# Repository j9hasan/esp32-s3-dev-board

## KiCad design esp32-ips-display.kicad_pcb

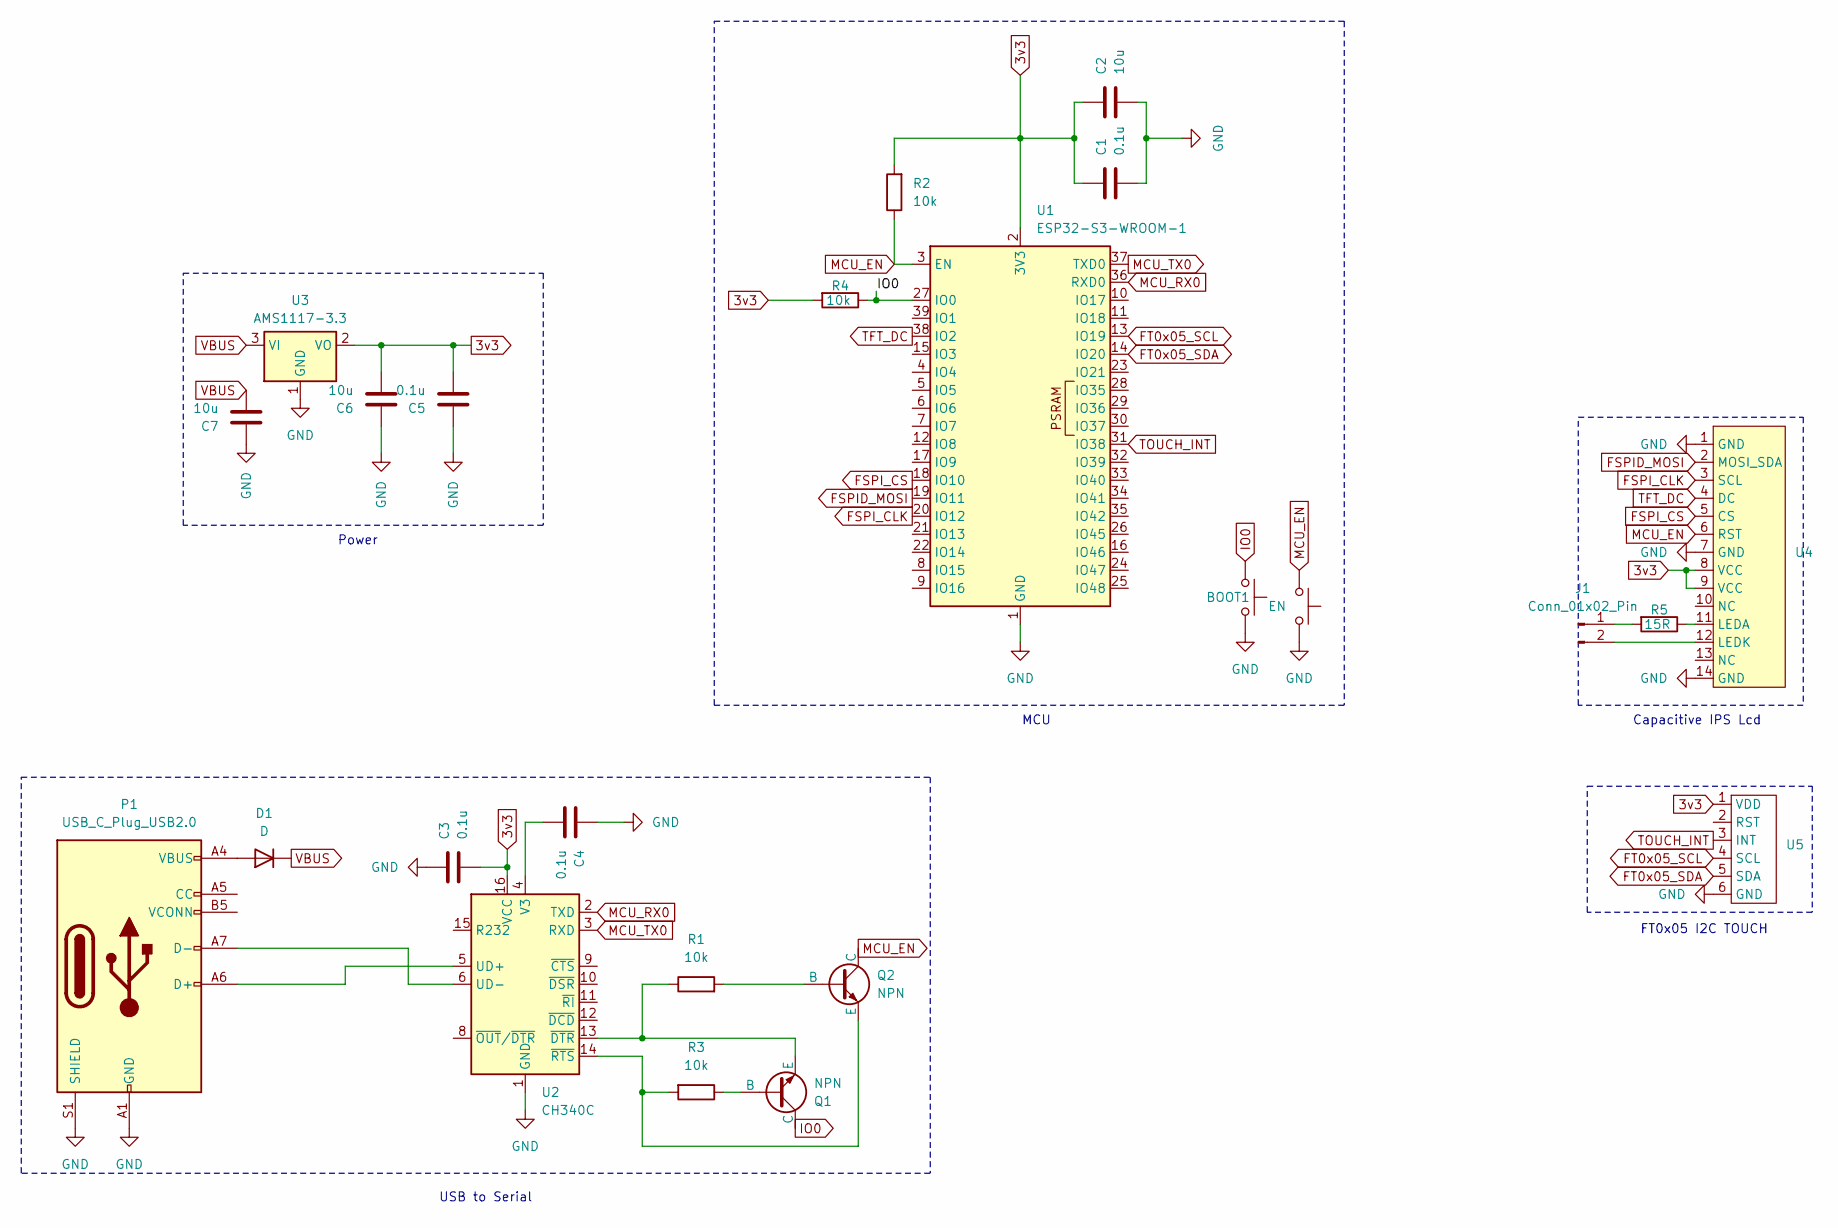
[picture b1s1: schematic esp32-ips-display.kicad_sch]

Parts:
BOOT1: BOOT; SW_Push_1P1T_NO_CK_KMR2
C1, C3, C4, C5: 0.1u; C_0805_2012Metric
C2, C6, C7: 10u; C_0805_2012Metric
D1: D; D_0805_2012Metric
EN1: EN; SW_Push_1P1T_NO_CK_KMR2
J1: Conn_01x02_Pin; TerminalBlock_Phoenix_PTSM-0,5-2-2,5-V-SMD_1x02-1MP_P2.50mm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
P1: USB_C_Plug_USB2.0; USB_C_Receptacle_GCT_USB4110
Q1, Q2: NPN; SOT-1123
R1: 10k; R_0805_2012Metric_Pad1.20x1.40mm_HandSolder
R2, R3, R4: 10k; R_0805_2012Metric
R5: 15R; R_0805_2012Metric
U1: ESP32-S3-WROOM-1
U2: CH340C; SOIC-16_3.9x9.9mm_P1.27mm
U3: AMS1117-3.3; SOT-223-3_TabPin2
U4: fpc_14_0.5
U5: FT0x05_I2C_Touch

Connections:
3v3: C1.1, C2.1, C3.2, C5.2, C6.2, R2.2, R4.2, U1.2 (3V3), U2.16 (VCC), U3.2 (VO), U4.8 (VCC), U4.9 (VCC), U5.1 (VDD)
FSPID_MOSI: U1.19 (IO11), U4.2 (MOSI_SDA)
FSPI_CLK: U1.20 (IO12), U4.3 (SCL)
FSPI_CS: U1.18 (IO10), U4.5 (CS)
FT0x05_SCL: U1.13 (IO19), U5.4 (SCL)
FT0x05_SDA: U1.14 (IO20), U5.5 (SDA)
GND: BOOT1.2, C1.2, C2.2, C3.1, C4.1, C5.1, C6.1, C7.1, EN1.2, P1.A1 (GND), P1.A12 (GND), P1.B1 (GND), P1.B12 (GND), P1.S1 (SHIELD), U1.1 (GND), U1.40 (GND), U1.41 (GND), U2.1 (GND), U3.1 (GND), U4.1 (GND), U4.7 (GND), U4.14 (GND), U5.6 (GND)
IO0: BOOT1.1, Q1.1 (C), R4.1, U1.27 (IO0)
MCU_EN: EN1.1, Q2.1 (C), R2.1, U1.3 (EN), U4.6 (RST); also elsewhere on the board
MCU_RX0: U1.36 (RXD0), U2.2 (TXD)
MCU_TX0: U1.37 (TXD0), U2.3 (RXD)
unnamed: D1.2 (A), P1.A4 (VBUS), P1.A9 (VBUS), P1.B4 (VBUS), P1.B9 (VBUS)
unnamed: J1.1, R5.2
unnamed: J1.2, U4.12 (LEDK)
unnamed: P1.A6 (D+), U2.5 (UD+)
unnamed: P1.A7 (D-), U2.6 (UD-)
unnamed: Q1.2 (B), R3.1
unnamed: Q1.3 (E), R1.1, U2.13 (~DTR)
unnamed: Q2.2 (B), R1.2
unnamed: Q2.3 (E), R3.2, U2.14 (~RTS)
unnamed: C4.2, U2.4 (V3)
unnamed: R5.1, U4.11 (LEDA)
TFT_DC: U1.38 (IO2), U4.4 (DC)
TOUCH_INT: U1.31 (IO38), U5.3 (INT)
VBUS: C7.2, D1.1 (K), U3.3 (VI)

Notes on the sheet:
Power
MCU
USB to Serial
FT0x05 I2C TOUCH
Capacitive IPS Lcd

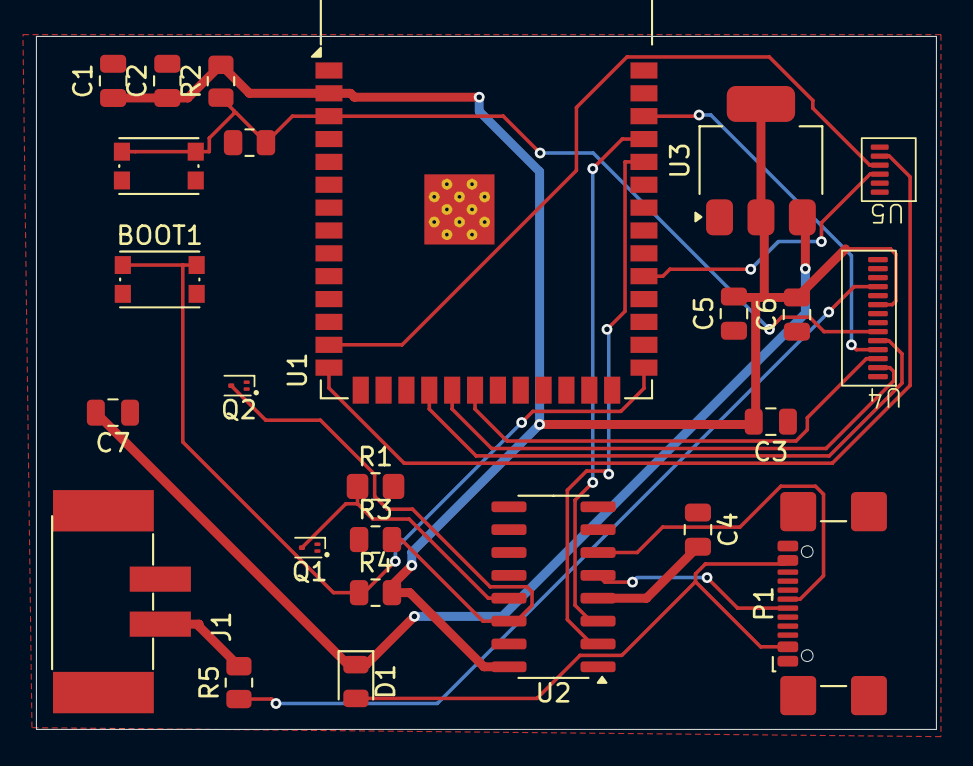
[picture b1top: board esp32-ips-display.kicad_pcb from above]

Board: 2 copper layers, 50.0 x 38.5 mm, 25 parts (0 on the bottom side), 25 nets.

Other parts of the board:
R10: R; R_0805_2012Metric

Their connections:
MCU_EN: R10.2; also elsewhere on the board
